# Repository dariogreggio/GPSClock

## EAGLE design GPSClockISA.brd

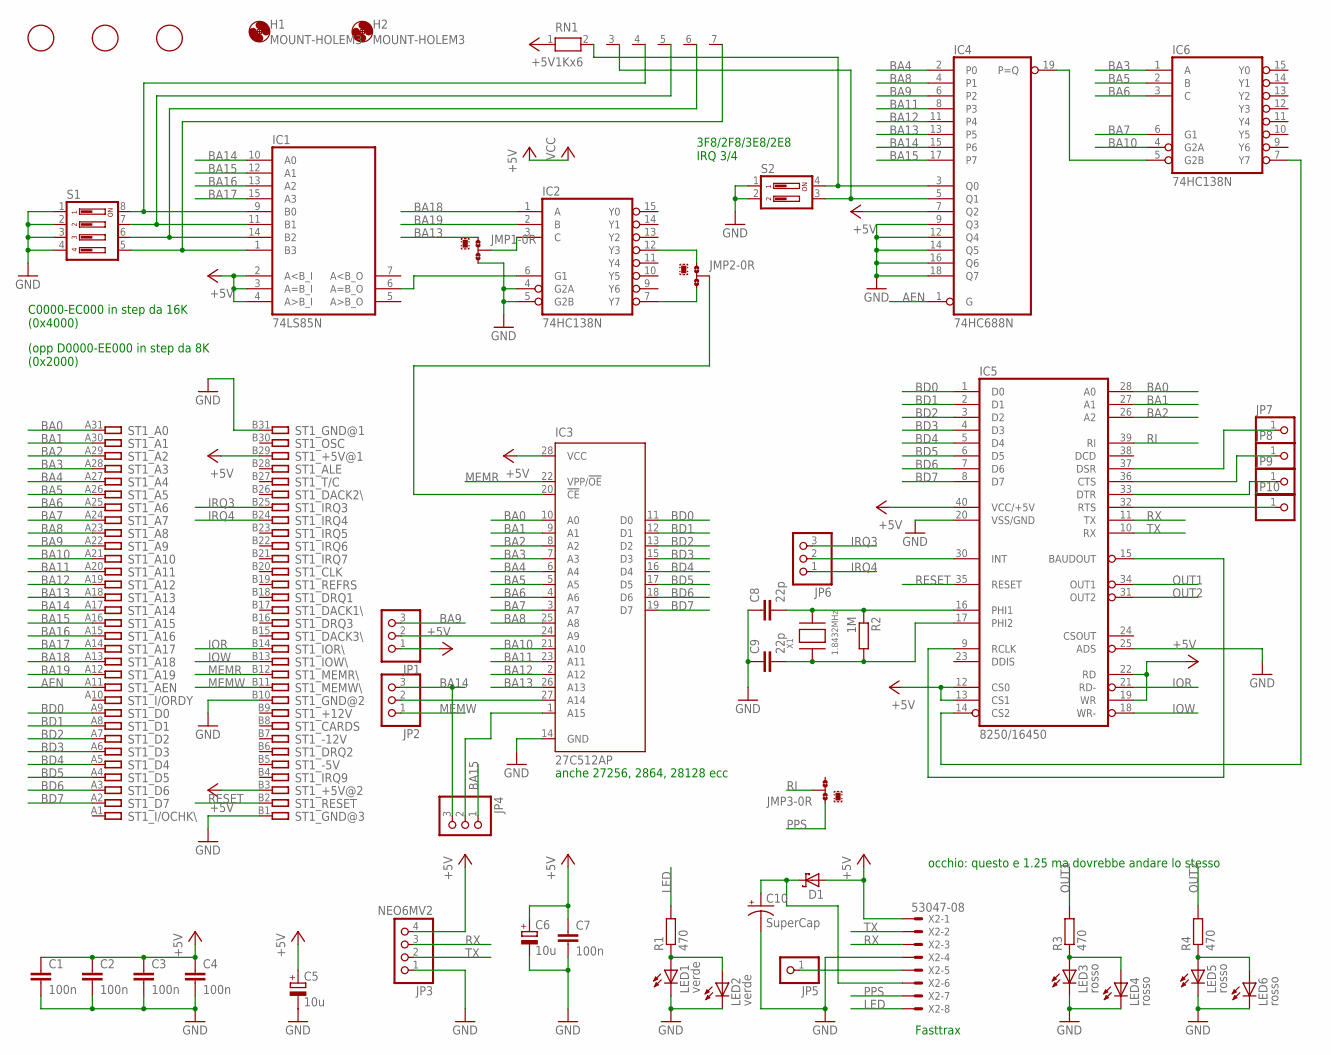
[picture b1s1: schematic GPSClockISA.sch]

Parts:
C1, C2, C3, C4, C7: 100n; C0805
C5: 10u; SMC_D
C6: 10u; SMC_C
C8, C9: 22p; C0805
C10: SuperCap; EB22,5D
D1: SCHOTTKY-DIODESMC; SMC
F1, F2, F3: FIDUCIAL; FIDUCIAL_1MM
H1, H2: MOUNT-HOLEM3; M3
IC1: 74LS85N; DIL16
IC2, IC6: 74HC138N; DIL16
IC3: 27C512AP; DIL28-6
IC4: 74HC688N; DIL20
IC5: 8250/16450; DIL40
JMP1, JMP2, JMP3: 0R-JUMPC; C0R-JMP
JP1, JP2, JP4, JP6: PINHD-1X03_2.54; 1X03
JP3: NEO6MV2; 1X04
JP5, JP7, JP8, JP9, JP10: PINHD-1X1; 1X01
LED1: verde; CHIPLED_0805
LED2: verde; LED3MM
LED3, LED5: rosso; CHIPLED_0805
LED4, LED6: rosso; LED3MM
R1, R3, R4: 470; R0805
R2: 1M; R0805
RN1: 1Kx6; RN-7
S1: DIP04YL
S2: DIP02YL
ST1: IBM8BIT
X1: 1.8432MHz; NX8045
X2: 53047-08

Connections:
+5V: C1.1, C2.1, C3.1, C4.1, C5.+, C6.+, C7.1, D1.A, IC1.2 (A<B_I), IC1.3 (A=B_I), IC1.4 (A>B_I), IC3.28 (VCC), IC4.7 (Q2), IC5.12 (CS0), IC5.13 (CS1), IC5.19 (WR), IC5.22 (RD), IC5.40 (VCC/+5V), JP1.1, JP3.4, RN1.1, ST1.B3, ST1.B29, X2.1
AEN: IC4.1 (G), ST1.A11
BA0: IC3.10 (A0), IC5.28 (A0), ST1.A31
BA1: IC3.9 (A1), IC5.27 (A1), ST1.A30
BA2: IC3.8 (A2), IC5.26 (A2), ST1.A29
BA3: IC3.7 (A3), IC6.1 (A), ST1.A28
BA4: IC3.6 (A4), IC4.2 (P0), ST1.A27
BA5: IC3.5 (A5), IC6.2 (B), ST1.A26
BA6: IC3.4 (A6), IC6.3 (C), ST1.A25
BA7: IC3.3 (A7), IC6.6 (G1), ST1.A24
BA8: IC3.25 (A8), IC4.4 (P1), ST1.A23
BA9: IC4.6 (P2), JP1.3, ST1.A22
BA10: IC3.21 (A10), IC6.4 (G2A), ST1.A21
BA11: IC3.23 (A11), IC4.8 (P3), ST1.A20
BA12: IC3.2 (A12), IC4.11 (P4), ST1.A19
BA13: IC3.26 (A13), IC4.13 (P5), JMP1.1, ST1.A18
BA14: IC1.10 (A0), IC4.15 (P6), JP2.3, JP4.3, ST1.A17
BA15: IC1.12 (A1), IC4.17 (P7), JP4.1, ST1.A16
BA16: IC1.13 (A2), ST1.A15
BA17: IC1.15 (A3), ST1.A14
BA18: IC2.1 (A), ST1.A13
BA19: IC2.2 (B), ST1.A12
BD0: IC3.11 (D0), IC5.1 (D0), ST1.A9
BD1: IC3.12 (D1), IC5.2 (D1), ST1.A8
BD2: IC3.13 (D2), IC5.3 (D2), ST1.A7
BD3: IC3.15 (D3), IC5.4 (D3), ST1.A6
BD4: IC3.16 (D4), IC5.5 (D4), ST1.A5
BD5: IC3.17 (D5), IC5.6 (D5), ST1.A4
BD6: IC3.18 (D6), IC5.7 (D6), ST1.A3
BD7: IC3.19 (D7), IC5.8 (D7), ST1.A2
GND: C1.2, C2.2, C3.2, C4.2, C5.-, C6.-, C7.2, C8.1, C9.1, C10.-, IC1.8 (GND), IC2.4 (G2A), IC2.5 (G2B), IC2.8 (GND), IC3.14 (GND), IC4.9 (Q3), IC4.10 (GND), IC4.12 (Q4), IC4.14 (Q5), IC4.16 (Q6), IC4.18 (Q7), IC5.20 (VSS/GND), IC5.25 (ADS), IC6.8 (GND), JMP1.3, JP3.1, LED1.C, LED2.K (C), LED3.C, LED4.K (C), LED5.C, LED6.K (C), S1.1, S1.2, S1.3, S1.4, S2.1, S2.2, ST1.B1, ST1.B10, ST1.B31, X2.4
IOR: IC5.21 (RD-), ST1.B14
IOW: IC5.18 (WR-), ST1.B13
IRQ3: JP6.3, ST1.B25
IRQ4: JP6.1, ST1.B24
LED: R1.2, X2.8
MEMR: IC3.22 (VPP/!OE), ST1.B12
MEMW: JP2.1, ST1.B11
unnamed: JP5.1, X2.5
unnamed: LED3.A, LED4.A, R3.1
unnamed: LED5.A, LED6.A, R4.1
unnamed: IC1.9 (B0), RN1.4, S1.8
unnamed: C10.+, D1.C, X2.6
unnamed: IC1.11 (B1), RN1.5, S1.7
unnamed: IC5.30 (INT), JP6.2
unnamed: IC1.14 (B2), RN1.6, S1.6
unnamed: LED1.A, LED2.A, R1.1
unnamed: IC1.1 (B3), RN1.7, S1.5
unnamed: IC2.12 (Y3), JMP2.1
unnamed: IC4.19 (P=Q), IC6.5 (G2B)
unnamed: IC3.20 (!CE), JMP2.2
unnamed: IC5.9 (RCLK), IC5.15 (BAUDOUT)
unnamed: C9.2, IC5.17 (PHI2), R2.2, X1.P$1
unnamed: IC3.27 (A14), JP2.2
unnamed: C8.2, IC5.16 (PHI1), R2.1, X1.P$2
unnamed: IC2.3 (C), JMP1.2
unnamed: IC3.1 (A15), JP4.2
unnamed: IC4.5 (Q1), RN1.3, S2.3
unnamed: IC4.3 (Q0), RN1.2, S2.4
unnamed: IC3.24 (A9), JP1.2
unnamed: IC1.6 (A=B_O), IC2.6 (G1)
unnamed: IC2.7 (Y7), JMP2.3
unnamed: IC5.14 (CS2), IC6.7 (Y7)
unnamed: IC5.37 (DSR), JP7.1
unnamed: IC5.36 (CTS), JP8.1
unnamed: IC5.33 (DTR), JP9.1
unnamed: IC5.32 (RTS), JP10.1
OUT1: IC5.34 (OUT1), R3.2
OUT2: IC5.31 (OUT2), R4.2
PPS: JMP3.1, X2.7
RESET: IC5.35 (RESET), ST1.B2
RI: IC5.39 (RI), JMP3.2
RX: IC5.11 (TX), JP3.3, X2.3
TX: IC5.10 (RX), JP3.2, X2.2
VCC: IC1.16 (VCC), IC2.16 (VCC), IC4.20 (VCC), IC6.16 (VCC)

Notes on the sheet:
occhio: questo e 1.25 ma dovrebbe andare lo stesso
Fasttrax
(opp D0000-EE000 in step da 8K (0x2000)
C0000-EC000 in step da 16K (0x4000)
3F8/2F8/3E8/2E8 IRQ 3/4
anche 27256, 2864, 28128 ecc

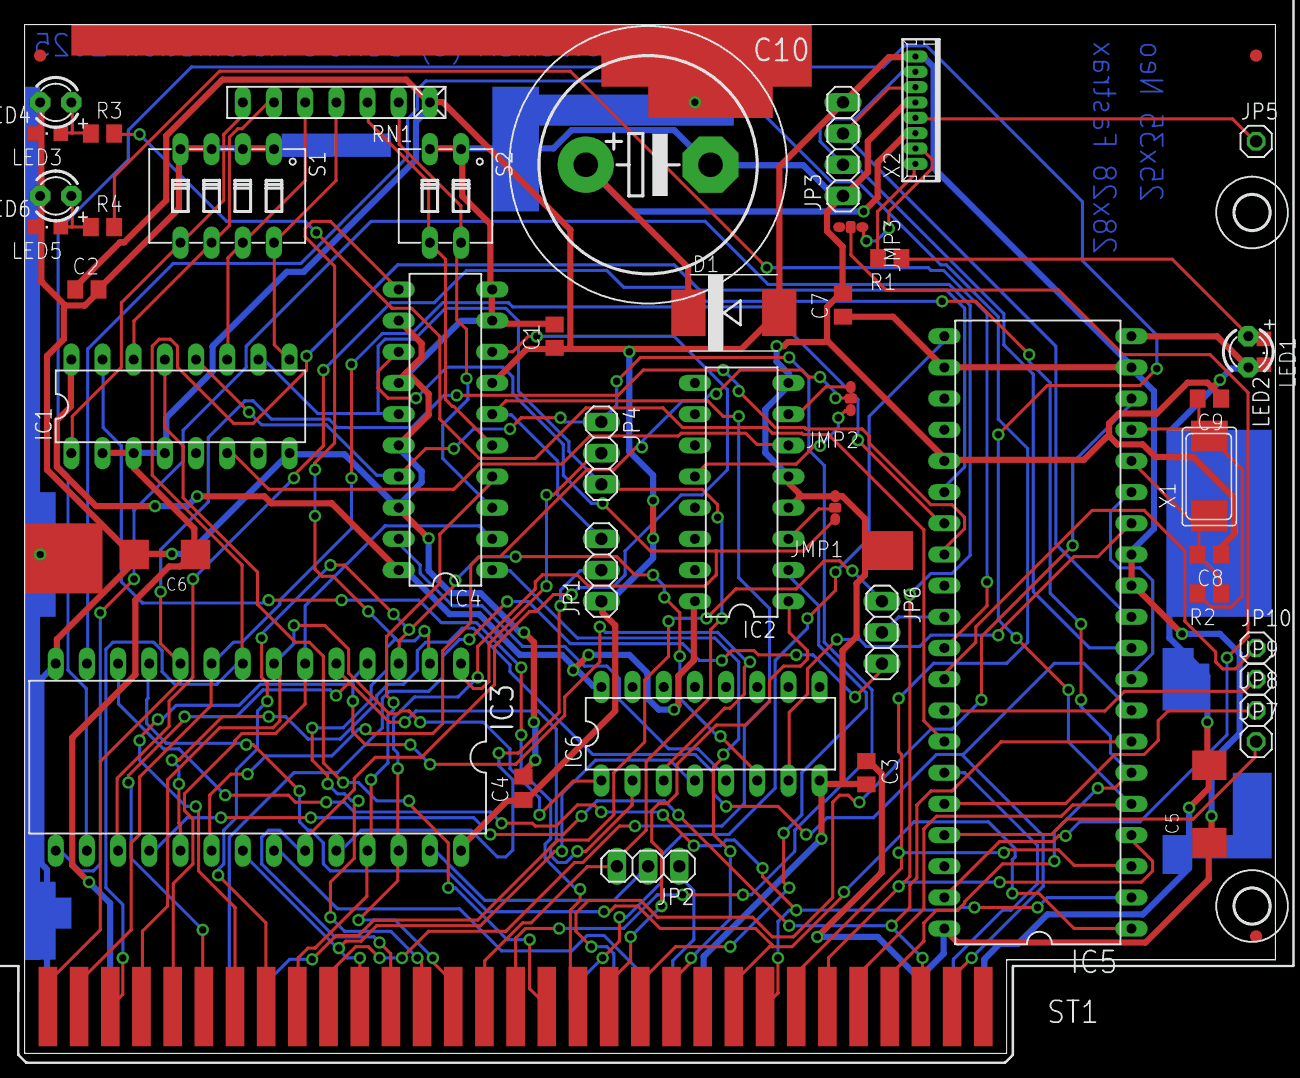
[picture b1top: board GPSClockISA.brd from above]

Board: 2 copper layers, 101.9 x 83.8 mm, 51 parts (0 on the bottom side), 75 nets.

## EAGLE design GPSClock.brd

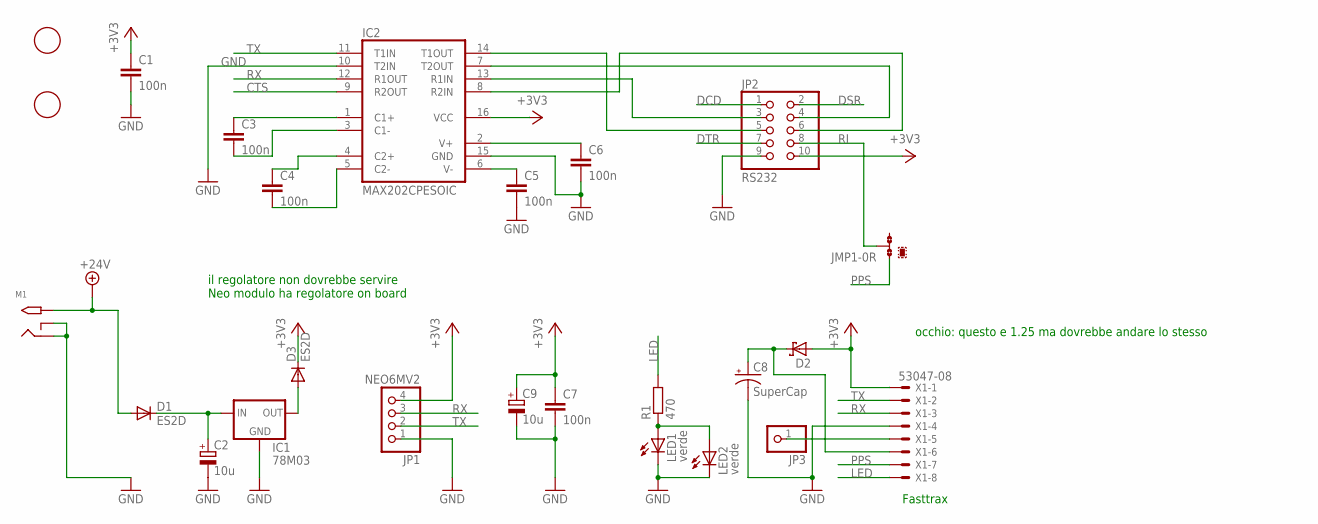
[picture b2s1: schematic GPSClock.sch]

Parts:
C1, C3, C4, C5, C6, C7: 100n; C0805
C2: 10u; SMC_D
C8: SuperCap; EB22,5D
C9: 10u; SMC_C
D1, D3: ES2D; SMB
D2: SCHOTTKY-DIODESMC; SMC
F2, F3: FIDUCIAL; FIDUCIAL_1MM
IC1: 78M03; DPACK
IC2: MAX202CPESOIC; SO16
JMP1: 0R-JUMPC; C0R-JMP
JP1: NEO6MV2; 1X04
JP2: RS232; 2X05
JP3: PINHD-1X1; 1X01
LED1: verde; CHIPLED_0805
LED2: verde; LED3MM
M1: 2.1MMJACKTHM; PJ-102A
R1: 470; R0805
X1: 53047-08

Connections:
+3V3: C1.1, C7.1, C9.+, D2.A, D3.C, IC2.16 (VCC), JP1.4, JP2.10, X1.1
+24V: D1.A, M1.TIP
CTS: IC2.9 (R2OUT)
DCD: JP2.1
DSR: JP2.2
DTR: JP2.7
GND: C1.2, C2.-, C5.2, C6.2, C7.2, C8.-, C9.-, IC1.4 (GND), IC2.10 (T2IN), IC2.15 (GND), JP1.1, JP2.9, LED1.C, LED2.K (C), M1.RING, M1.RING_SW, X1.4
LED: R1.2, X1.8
unnamed: JP3.1, X1.5
unnamed: C3.1, IC2.1 (C1+)
unnamed: D3.A, IC1.3 (OUT)
unnamed: C3.2, IC2.3 (C1-)
unnamed: C8.+, D2.C, X1.6
unnamed: C2.+, D1.C, IC1.1 (IN)
unnamed: LED1.A, LED2.A, R1.1
unnamed: C4.1, IC2.4 (C2+)
unnamed: C4.2, IC2.5 (C2-)
unnamed: IC2.14 (T1OUT), JP2.5
unnamed: IC2.7 (T2OUT), JP2.4
unnamed: IC2.13 (R1IN), JP2.3
unnamed: IC2.8 (R2IN), JP2.6
PPS: JMP1.1, X1.7
RI: JMP1.2, JP2.8
RX: IC2.12 (R1OUT), JP1.3, X1.3
TX: IC2.11 (T1IN), JP1.2, X1.2
V+: C6.1, IC2.2 (V+)
V-: C5.1, IC2.6 (V-)

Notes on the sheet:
occhio: questo e 1.25 ma dovrebbe andare lo stesso
Fasttrax
il regolatore non dovrebbe servire Neo modulo ha regolatore on board

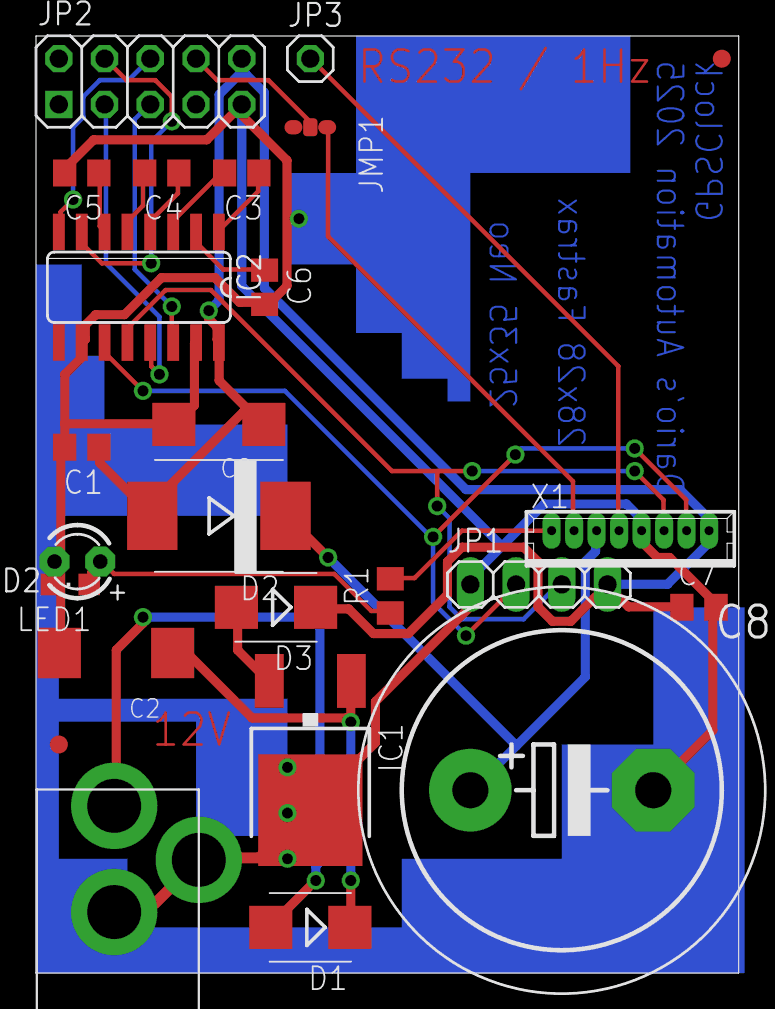
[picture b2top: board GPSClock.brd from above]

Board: 2 copper layers, 39.0 x 52.1 mm, 25 parts (0 on the bottom side), 23 nets.

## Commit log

2025-07-20 Eagle CAD files
2025-07-20 an ISA card featuring GPS module, for time syncing
